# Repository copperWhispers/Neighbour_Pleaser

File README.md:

# Neighbour_Pleaser
A device that will please your neighborhood so that you don't make any life threatening enemies.
Also teaches how to convert Sound into voltage, precision rectifiers, opamps, comparators..

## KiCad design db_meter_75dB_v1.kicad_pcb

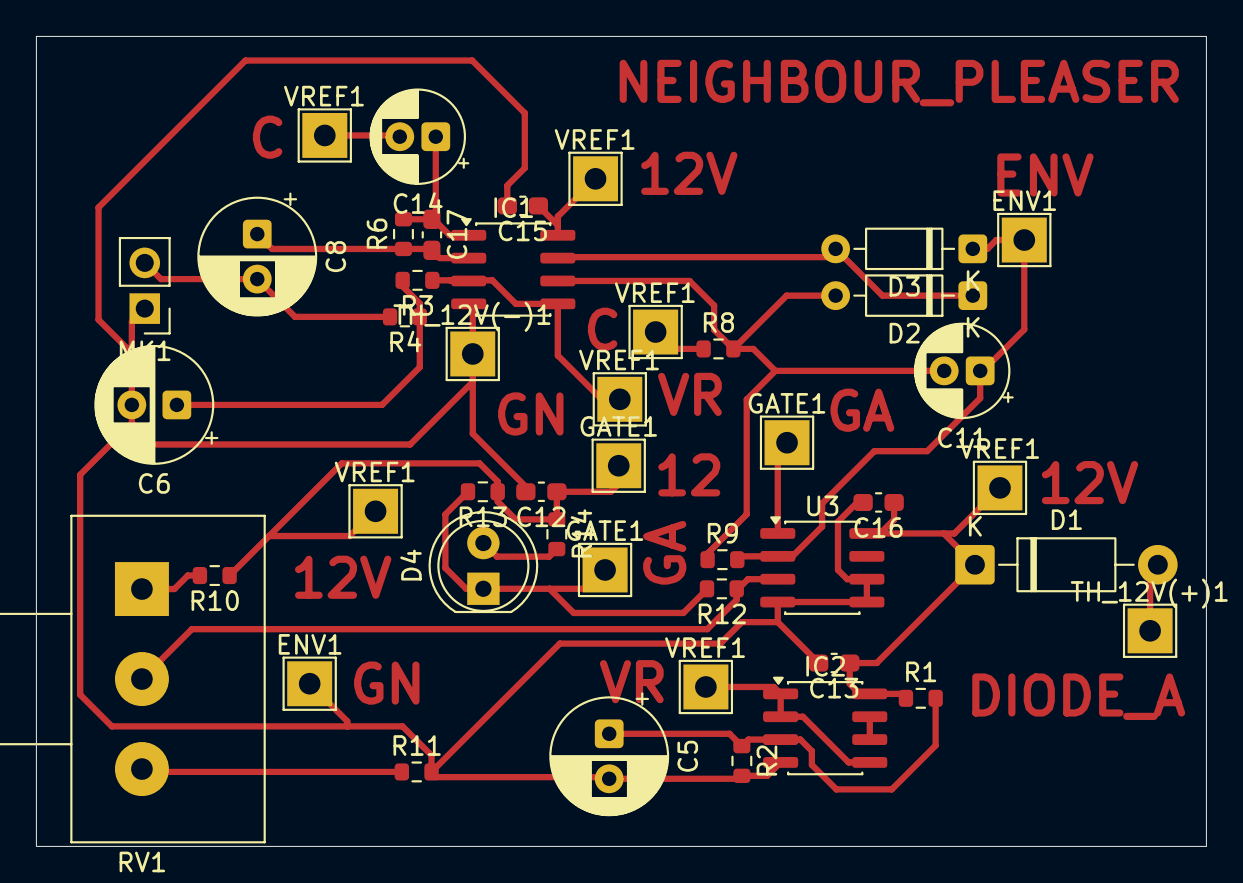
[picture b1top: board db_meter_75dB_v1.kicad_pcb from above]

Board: 2 copper layers, 65.0 x 45.0 mm, 45 parts (0 on the bottom side), 19 nets.

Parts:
C5, C6: 100u; CP_Radial_D6.3mm_P2.50mm
C8: 10u; CP_Radial_D6.3mm_P2.50mm
C11: 4.7u; CP_Radial_D5.0mm_P2.00mm
C12, C13, C15: 100n; C_0603_1608Metric_Pad1.08x0.95mm_HandSolder
C14: 10u; CP_Radial_D5.0mm_P2.00mm
C16: 10u; C_0603_1608Metric_Pad1.08x0.95mm_HandSolder
C17: 47p; C_0603_1608Metric_Pad1.08x0.95mm_HandSolder
D1: 1N4001; D_DO-41_SOD81_P10.16mm_Horizontal
D2, D3: 1N4148; D_DO-35_SOD27_P7.62mm_Horizontal
D4: RED; LED_D5.0mm
ENV1, ENV1#2: TestPoint_THTPad_2.5x2.5mm_Drill1.2mm
GATE1, GATE1#2, GATE1#3: TestPoint_THTPad_2.5x2.5mm_Drill1.2mm
IC1, IC2: NE5532P; SOIC-8_3.9x4.9mm_P1.27mm
MK1: Electret; PinHeader_1x02_P2.54mm_Vertical
R1, R2, R13: 10k; R_0603_1608Metric
R3: 100; R_0603_1608Metric
R4: 2.2k; R_0603_1608Metric
R6, R9: 220k; R_0603_1608Metric
R8: 15k8; R_0603_1608Metric
R10: 7k5; R_0603_1608Metric
R11: 9k1; R_0603_1608Metric
R12: 1M; R_0603_1608Metric
R14: 4k7; R_0603_1608Metric
RV1: 1k trimmer; Potentiometer_Alps_RK163_Single_Horizontal
TH_12V(+)1, TH_12V(-)1: TestPoint_THTPad_2.5x2.5mm_Drill1.2mm
U3: LM393D; SOIC-8_3.9x4.9mm_P1.27mm
VREF1, VREF1#2, VREF1#3, VREF1#4, VREF1#5, VREF1#6, VREF1#7: TestPoint_THTPad_2.5x2.5mm_Drill1.2mm

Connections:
+12V: C12.1, C13.1, C15.1, C16.1, D1.1 (K), GATE1.1, IC1.8 (VCC+), IC2.8 (VCC+), R1.1, R10.1, R13.1, R14.1, U3.8 (VCC+), VREF1.1, VREF1#6.1, VREF1#7.1
/ENV: C11.1, D3.1 (K), ENV1.1, R9.2, U3.2 (IN1-)
/GATE: D4.1 (K), GATE1#2.1, GATE1#3.1, R12.2, R13.2, U3.1 (OUT1)
/OUT_AMP2: D2.1 (K), D3.2 (A), IC1.7 (2OUT)
/VREF: IC1.3 (1IN+), IC1.5 (2IN+), IC2.1 (1OUT), IC2.2 (1IN-), IC2.5 (2IN+), R3.1, VREF1#2.1, VREF1#3.1
/Vtrigger: R12.1, RV1.2, U3.3 (IN1+)
GND: C5.2, C6.2, C12.2, C13.2, C15.2, C16.2, ENV1#2.1, IC1.4 (VCC-), IC2.4 (VCC-), MK1.1 (-), R2.2, R11.2, TH_12V(-)1.1, U3.4 (VCC-), U3.5 (IN2+), U3.6 (IN2-)
unnamed: C6.1, R3.2, R4.1
unnamed: C14.2, R8.1, VREF1#4.1, VREF1#5.1
unnamed: D1.2 (A), TH_12V(+)1.1
unnamed: C11.2, D2.2 (A), IC1.6 (2IN-), R8.2, R9.1
unnamed: D4.2 (A), R14.2
unnamed: C8.1, C17.2, IC1.2 (1IN-), R6.1
unnamed: C14.1, C17.1, IC1.1 (1OUT), R6.2
unnamed: C5.1, IC2.3 (1IN+), R1.2, R2.1
unnamed: IC2.6 (2IN-), IC2.7 (2OUT)
unnamed: C8.2, MK1.2 (+), R4.2
unnamed: R10.2, RV1.1
unnamed: R11.1, RV1.3
